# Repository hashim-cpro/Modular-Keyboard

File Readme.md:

<div align="center">
  <a href="https://hackclub.com/highway">
    </img>
  </a>
  
<h1>60% Modular Keyboard</h1>
</div>

It is a 60% wireless keyboard(bluetooth) also works wired. It has magnetic modules. Currently I only added a Numpad but almost anything could be added in a chain as long as it works on i2c.
it has hotswapable switches, rgb lights for each key, OLED, rotoary encoder, dedicated charging module(1000mah) and a 10000mah battery. Also it is kind of MCU agnostic, you can use any XIAO series MCU with it, for example rp2040 if you don't want bluetooth or nRF52840.

# CAD Design

I used shapr3d to make the case, it is not done, I am still working on it, once I am happy with a case I will add it here, but the current case is as follows:

# Wired connections

The charging module and battery are not connected to the PCB electrically, I will use wires for them.

# PCB design

I used KiCad to make the PCB. Here are the schematics:

Here is the PCB:

# Firmware

For Firmware I made two versions:

1. **QMK Firmware**: Works out of the box but it is wired only (no Bluetooth). This is ready to use.
2. **ZMK Firmware**: Supports Bluetooth wireless functionality. This will work only when ZMK is upgraded to Zephyr 3.6 or with a custom driver for the I2C expander.

Both firmware options are available in this repository under the Firmware directory.

# BOM

here's the csv: [Link](https://docs.google.com/spreadsheets/d/1DyREVeE_MUjtT9r5M6x5S8JvudkvJUOvS-f6R7vg9m8/edit?usp=sharing)
| Name | Quantity | Price (USD) | Shipping Cost (USD) | URL |
| ------------------------- | ------------------ | ----------- | ------------------- | --- |
| [Switches](https://www.aliexpress.com/item/1005008458590123.html) | 90 | $35.73 | $0.00 | [Link](https://www.aliexpress.com/item/1005008458590123.html) |
| [Keycaps](https://www.aliexpress.com/item/1005006068241056.html) | 1 | $23.25 | $0.00 | [Link](https://www.aliexpress.com/item/1005006068241056.html) |
| [Hotswapable sockets](https://www.aliexpress.com/item/1005009187521124.html) | 110 | $15.39 | $0.00 | [Link](https://www.aliexpress.com/item/1005009187521124.html) |
| [Stabilizers](https://www.aliexpress.com/item/1005001686299616.html) | 1x set | $10.77 | $0.00 | [Link](https://www.aliexpress.com/item/1005001686299616.html) |
| Custom PCB | 5 | $20.00 | $25.00 | jlcpcb |
| [Magnetic pogo pins](https://www.aliexpress.com/item/1005008564171277.html) | 2x 3p and 2x 4p | $20.28 | $0.00 | [Link](https://www.aliexpress.com/item/1005008564171277.html) |
| [Microcontroller](https://www.aliexpress.com/item/1005007416714633.html) | 1 | $10.27 | $5.00 | [Link](https://www.aliexpress.com/item/1005007416714633.html) |
| [I2C expander](https://www.aliexpress.com/item/1005008705264264.html?spm=a2g0o.productlist.main.11.68e87c79MkEB3P&algo_pvid=652b9ee5-a6ca-4eb2-a04e-750bf44d7567&algo_exp_id=652b9ee5-a6ca-4eb2-a04e-750bf44d7567-10&pdp_ext_f=%7B%22order%22%3A%22-1%22%2C%22eval%22%3A%221%22%7D&pdp_npi=6%40dis%21USD%215.04%215.04%21%21%2136.00%2136.00%21%402101246417554269745763126e6e24%2112000046323693257%21sea%21PK%212630002641%21ABX%211%210%21n_tag%3A-29910%3Bm03_new_user%3A-29895&curPageLogUid=tP3Bol6SwU30&utparam-url=scene%3Asearch%7Cquery_from%3A%7Cx_object_id%3A1005008705264264%7C_p_origin_prod%3A) | 2 | $5.04 | $3.47 | [Link](https://www.aliexpress.com/item/1005008705264264.html?spm=a2g0o.productlist.main.11.68e87c79MkEB3P&algo_pvid=652b9ee5-a6ca-4eb2-a04e-750bf44d7567&algo_exp_id=652b9ee5-a6ca-4eb2-a04e-750bf44d7567-10&pdp_ext_f=%7B%22order%22%3A%22-1%22%2C%22eval%22%3A%221%22%7D&pdp_npi=6%40dis%21USD%215.04%215.04%21%21%2136.00%2136.00%21%402101246417554269745763126e6e24%2112000046323693257%21sea%21PK%212630002641%21ABX%211%210%21n_tag%3A-29910%3Bm03_new_user%3A-29895&curPageLogUid=tP3Bol6SwU30&utparam-url=scene%3Asearch%7Cquery_from%3A%7Cx_object_id%3A1005008705264264%7C_p_origin_prod%3A) |
| [Battery](https://www.aliexpress.com/item/1005001651303033.html) | 1 | $6.30 | $0.00 | [Link](https://www.aliexpress.com/item/1005001651303033.html) |
| [Battery protection module](https://www.aliexpress.com/item/1005007507131765.html) | 1 | $4.00 | $0.00 | [Link](https://www.aliexpress.com/item/1005007507131765.html) |
| Charging module | Will supply myself | $0.00 | $0.00 | - |
| Boost converter | Will supply myself | $0.00 | $0.00 | - |
| Rotatory Encoder | Already owned | $0.00 | $0.00 | - |
| [OLED module](https://www.aliexpress.com/item/1005006351390199.html) | 1 | $5.00 | $0.00 | [Link](https://www.aliexpress.com/item/1005006351390199.html) |
| [SK6812 mini E leds](https://www.aliexpress.com/item/1005008417206409.html) | 100 | $4.88 | $3.11 | [Link](https://www.aliexpress.com/item/1005008417206409.html) |
| [Diodes](https://digilog.pk/products/in4148-1n-4148-diode) | 100 | $1.00 | $1.00 | [Link](https://digilog.pk/products/in4148-1n-4148-diode) |
| **Total** | | **$161.55** | **$43.40** | |
| **Complete Cost** | | **$204.95** | | |

> The complete cost does not include the 3D printed case.

**Important Note**: You might find some of these components cheaper on AliExpress, but trust me, their shipping costs to Pakistan are absolutely insane. I created this BOM keeping Pakistani shipping costs in mind - sometimes paying a bit more upfront is way better than getting hit with crazy shipping fees later. If you're in a different country, definitely check AliExpress for better deals, but for us Pakistanis, this is probably your best bet cost-wise.

Also Ali Express prices tend to change for different regions, so when verifying the BOM, make sure to set the region to Pakistan to get the correct prices.

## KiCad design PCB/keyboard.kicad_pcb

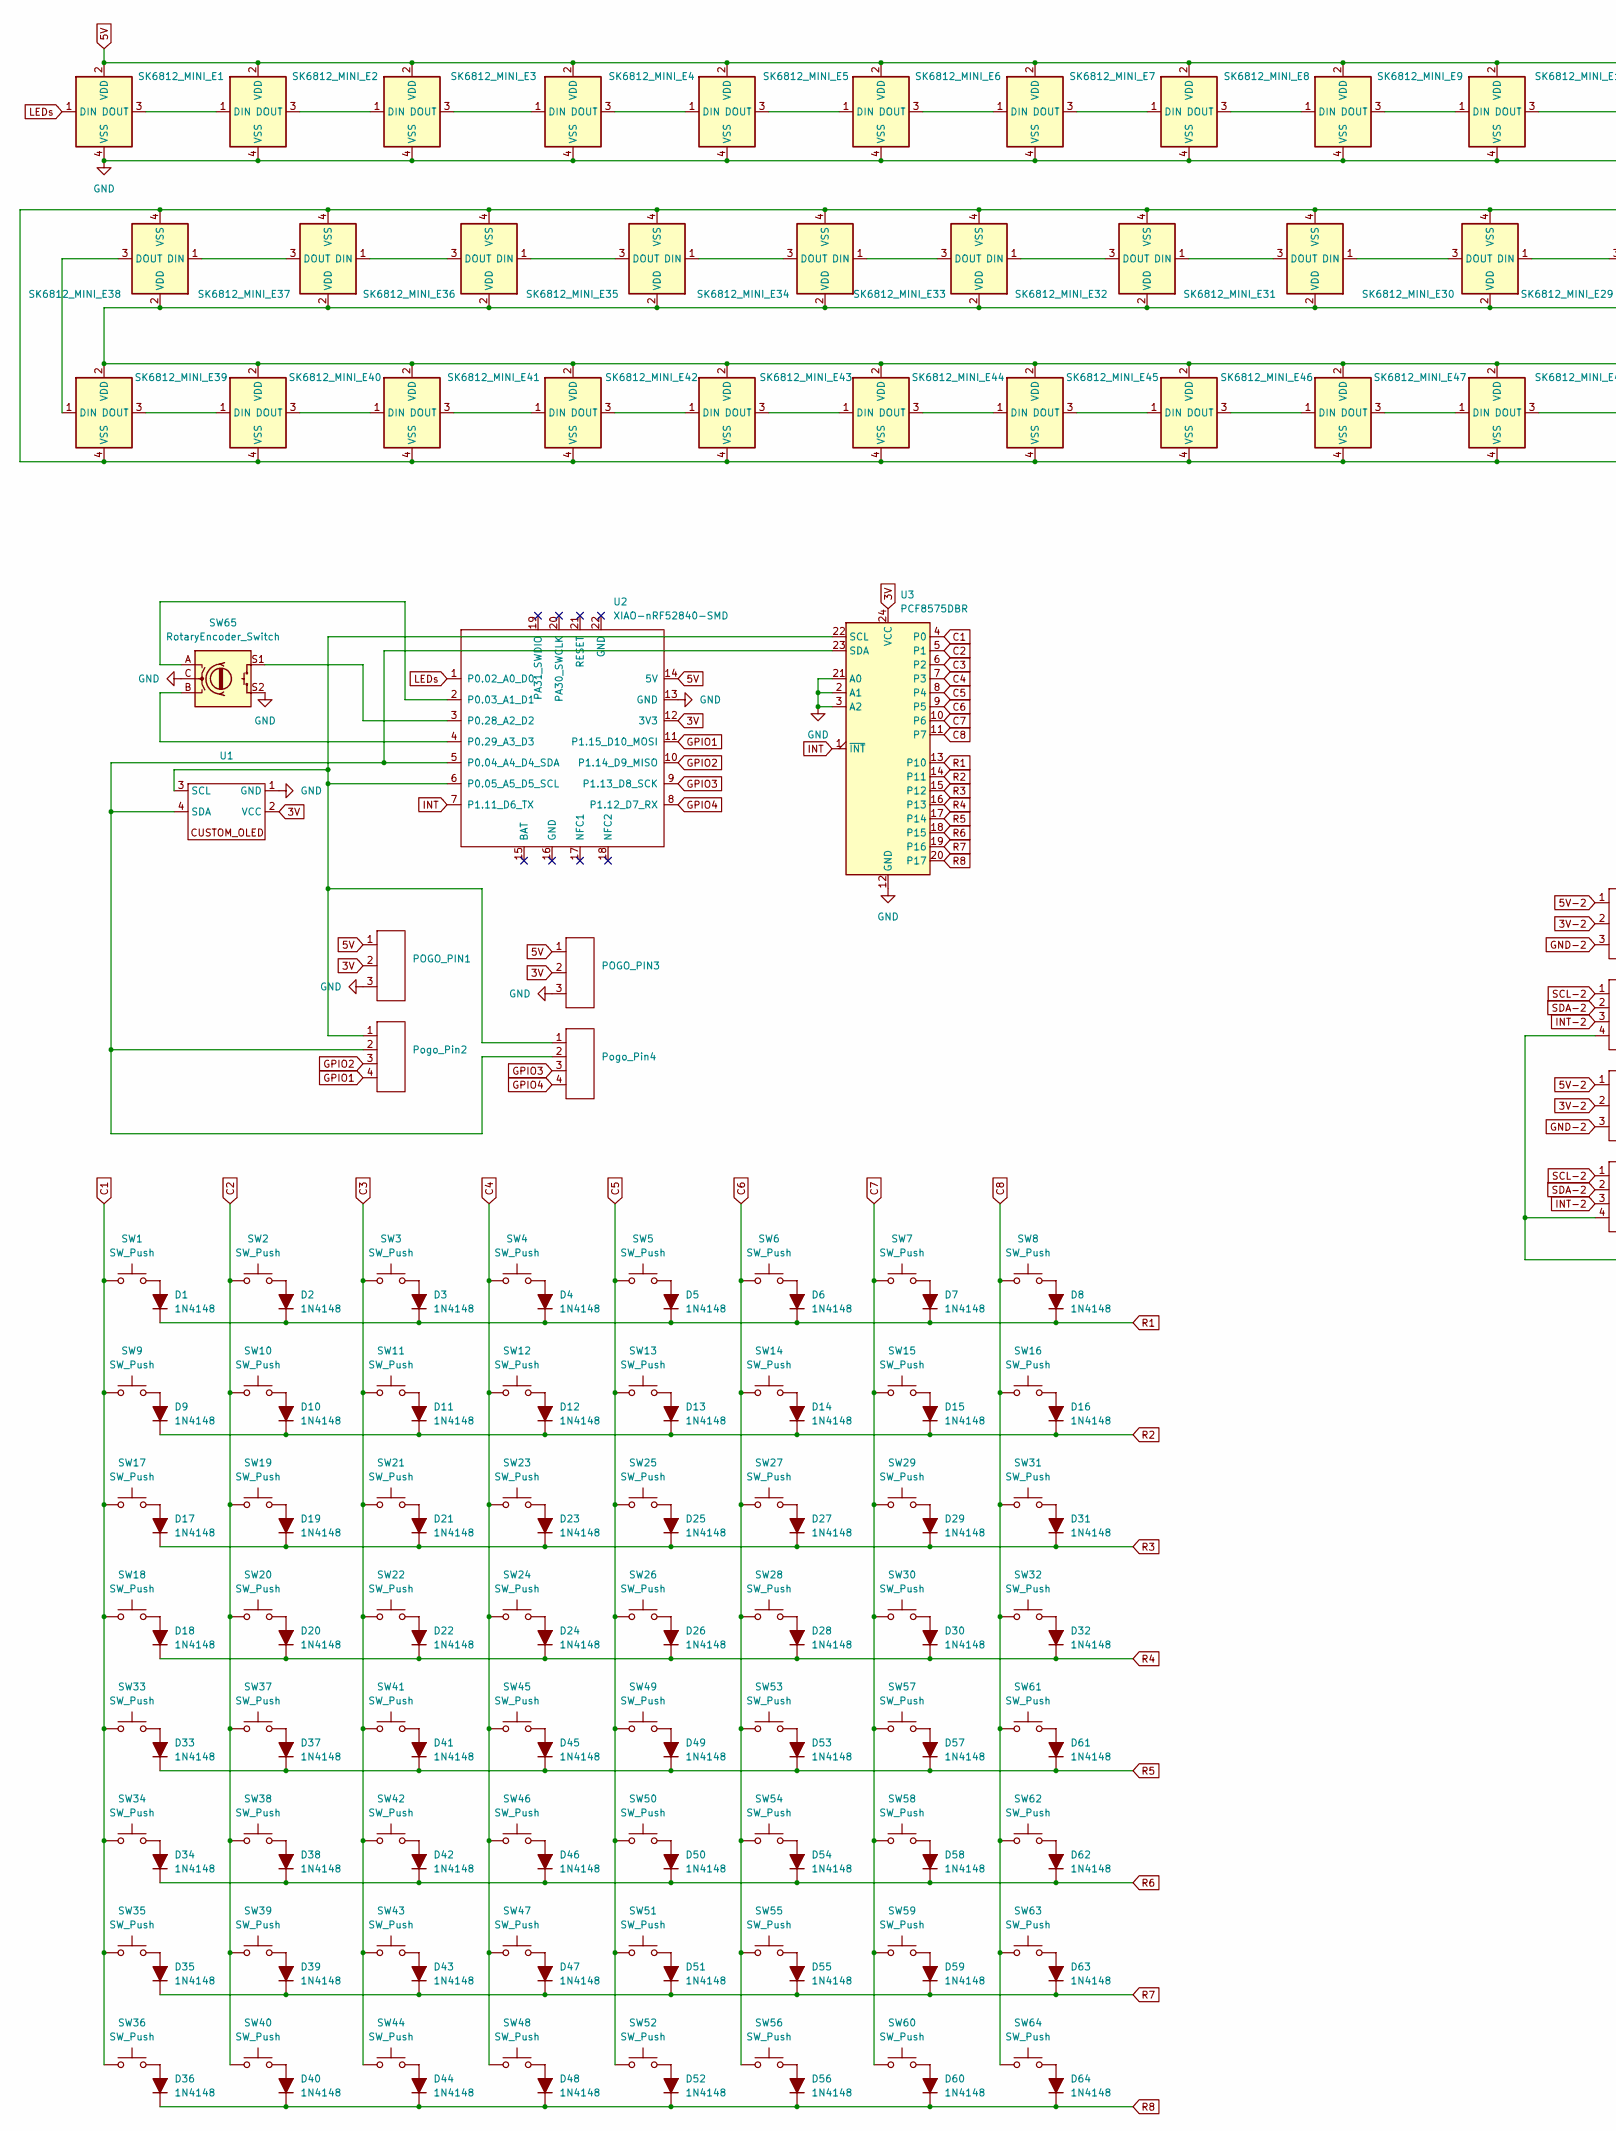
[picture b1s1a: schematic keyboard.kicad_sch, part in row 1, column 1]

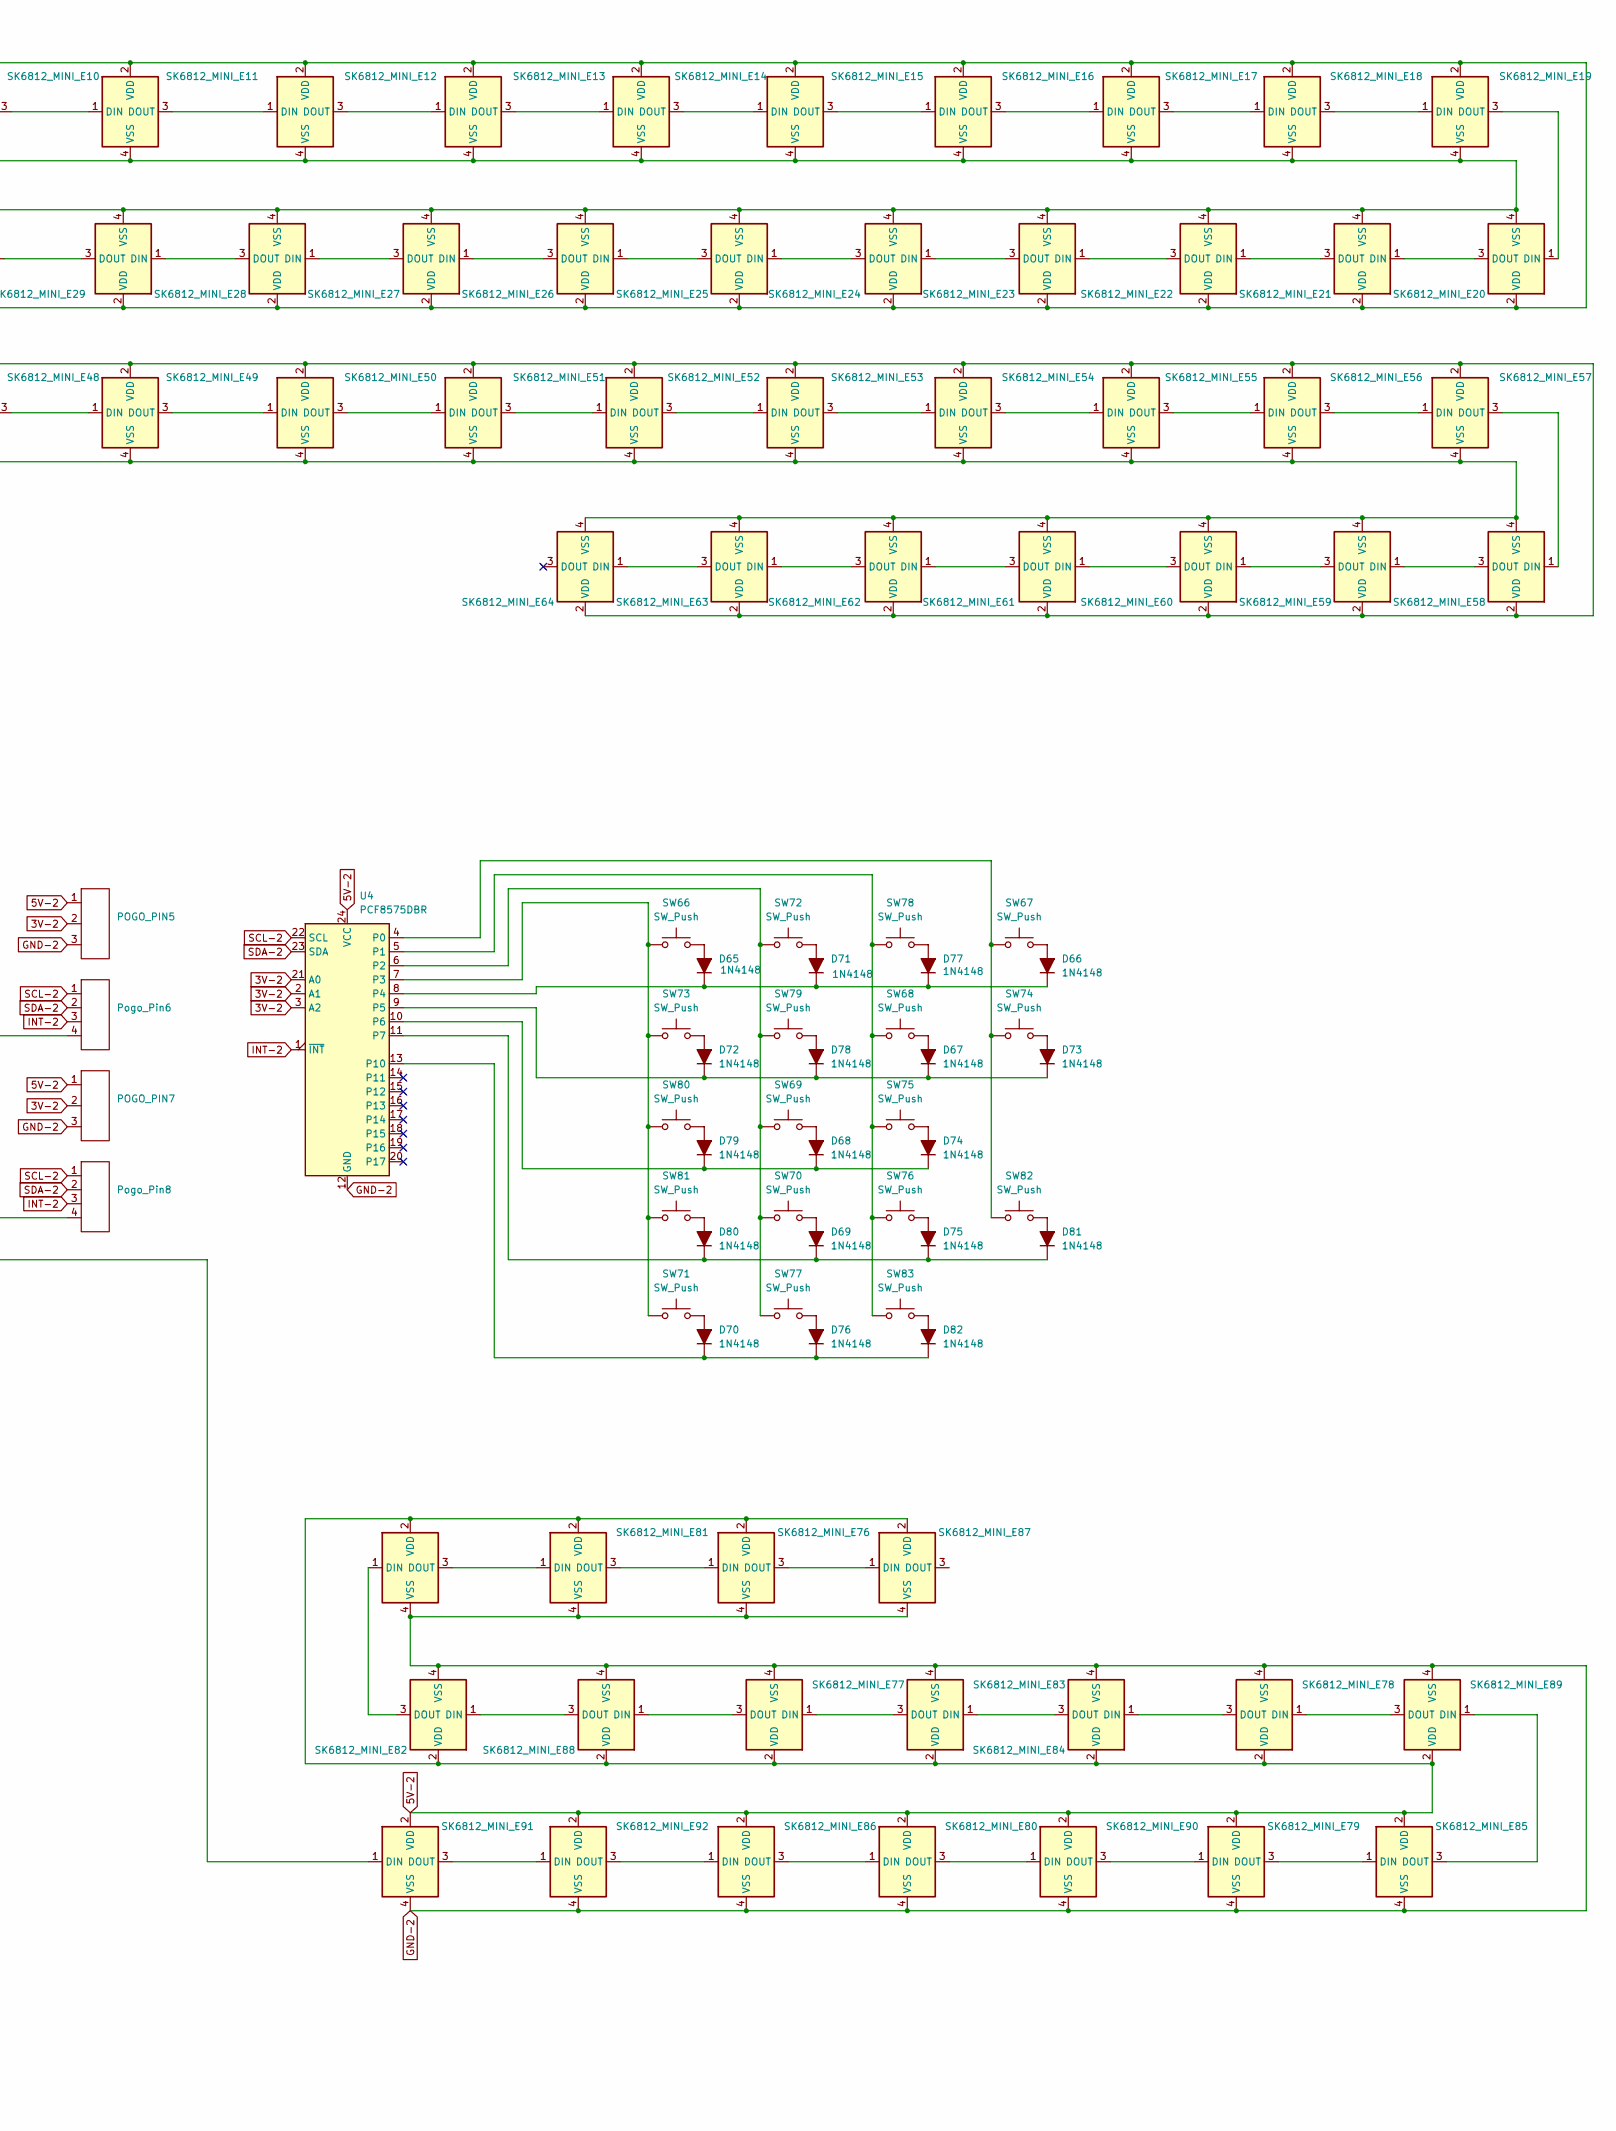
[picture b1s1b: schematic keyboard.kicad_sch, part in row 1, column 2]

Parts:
D1, D2, D3, D4, D5, D6, D7, D8, D9, D10, D11, D12, D13, D14, D15, D16, D17, D18, D19, D20, D21, D22, D23, D24, D25, D26, D27, D28, D29, D30, D31, D32, D33, D34, D35, D36, D37, D38, D39, D40, D41, D42, D43, D44, D45, D46, D47, D48, D49, D50, D51, D52, D53, D54, D55, D56, D57, D58, D59, D60, D61, D62, D63, D64, D65, D66, D67, D68, D69, D70, D71, D72, D73, D74, D75, D76, D77, D78, D79, D80, D81, D82: 1N4148; D_DO-35_SOD27_P7.62mm_Horizontal
POGO_PIN1, POGO_PIN3, POGO_PIN5, POGO_PIN7: Pogo_Pins_3P
Pogo_Pin2, Pogo_Pin4, Pogo_Pin6, Pogo_Pin8: Pogo_Pins_4P
SK6812_MINI_E1, SK6812_MINI_E2, SK6812_MINI_E3, SK6812_MINI_E4, SK6812_MINI_E5, SK6812_MINI_E6, SK6812_MINI_E7, SK6812_MINI_E8, SK6812_MINI_E9, SK6812_MINI_E10, SK6812_MINI_E11, SK6812_MINI_E12, SK6812_MINI_E13, SK6812_MINI_E14, SK6812_MINI_E15, SK6812_MINI_E16, SK6812_MINI_E17, SK6812_MINI_E18, SK6812_MINI_E19, SK6812_MINI_E20, SK6812_MINI_E21, SK6812_MINI_E22, SK6812_MINI_E23, SK6812_MINI_E24, SK6812_MINI_E25, SK6812_MINI_E26, SK6812_MINI_E27, SK6812_MINI_E28, SK6812_MINI_E29, SK6812_MINI_E30, SK6812_MINI_E31, SK6812_MINI_E32, SK6812_MINI_E33, SK6812_MINI_E34, SK6812_MINI_E35, SK6812_MINI_E36, SK6812_MINI_E37, SK6812_MINI_E38, SK6812_MINI_E39, SK6812_MINI_E40, SK6812_MINI_E41, SK6812_MINI_E42, SK6812_MINI_E43, SK6812_MINI_E44, SK6812_MINI_E45, SK6812_MINI_E46, SK6812_MINI_E47, SK6812_MINI_E48, SK6812_MINI_E49, SK6812_MINI_E50, SK6812_MINI_E51, SK6812_MINI_E52, SK6812_MINI_E53, SK6812_MINI_E54, SK6812_MINI_E55, SK6812_MINI_E56, SK6812_MINI_E57, SK6812_MINI_E58, SK6812_MINI_E59, SK6812_MINI_E60, SK6812_MINI_E61, SK6812_MINI_E62, SK6812_MINI_E63, SK6812_MINI_E64, SK6812_MINI_E75, SK6812_MINI_E76, SK6812_MINI_E77, SK6812_MINI_E78, SK6812_MINI_E79, SK6812_MINI_E80, SK6812_MINI_E81, SK6812_MINI_E82, SK6812_MINI_E83, SK6812_MINI_E84, SK6812_MINI_E85, SK6812_MINI_E86, SK6812_MINI_E87, SK6812_MINI_E88, SK6812_MINI_E89, SK6812_MINI_E90, SK6812_MINI_E91, SK6812_MINI_E92: MX_SK6812MINI-E
SW1, SW2, SW3, SW4, SW5, SW6, SW7, SW8, SW9, SW10, SW11, SW12, SW13, SW14, SW15, SW16, SW17, SW18, SW19, SW20, SW21, SW22, SW23, SW24, SW25, SW26, SW27, SW28, SW29, SW30, SW31, SW32, SW33, SW34, SW35, SW36, SW37, SW38, SW39, SW40, SW41, SW42, SW43, SW44, SW45, SW46, SW47, SW48, SW49, SW50, SW51, SW52, SW53, SW54, SW55, SW56, SW57, SW58, SW59, SW60, SW61, SW62, SW63, SW64, SW66, SW67, SW68, SW69, SW70, SW71, SW72, SW73, SW74, SW75, SW76, SW77, SW78, SW79, SW80, SW81, SW82, SW83: SW_Push; SW_Hotswap_Kailh_MX_1.00u
SW65: RotaryEncoder_Switch; RotaryEncoder_Alps_EC11E-Switch_Vertical_H20mm
U1: SSD1306-0.91-OLED-4pin-128x32
U2: XIAO-nRF52840-SMD; XIAO-nRF52840-DIP
U3, U4: PCF8575DBR; SSOP-24_5.3x8.2mm_P0.65mm

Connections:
3V: POGO_PIN1.2, POGO_PIN3.2, U1.2 (VCC), U2.12 (3V3), U3.24 (VCC)
3V-2: POGO_PIN5.2, POGO_PIN7.2, U4.2 (A1), U4.3 (A2), U4.21 (A0)
5V: POGO_PIN1.1, POGO_PIN3.1, SK6812_MINI_E1.2 (VDD), SK6812_MINI_E2.2 (VDD), SK6812_MINI_E3.2 (VDD), SK6812_MINI_E4.2 (VDD), SK6812_MINI_E5.2 (VDD), SK6812_MINI_E6.2 (VDD), SK6812_MINI_E7.2 (VDD), SK6812_MINI_E8.2 (VDD), SK6812_MINI_E9.2 (VDD), SK6812_MINI_E10.2 (VDD), SK6812_MINI_E11.2 (VDD), SK6812_MINI_E12.2 (VDD), SK6812_MINI_E13.2 (VDD), SK6812_MINI_E14.2 (VDD), SK6812_MINI_E15.2 (VDD), SK6812_MINI_E16.2 (VDD), SK6812_MINI_E17.2 (VDD), SK6812_MINI_E18.2 (VDD), SK6812_MINI_E19.2 (VDD), SK6812_MINI_E20.2 (VDD), SK6812_MINI_E21.2 (VDD), SK6812_MINI_E22.2 (VDD), SK6812_MINI_E23.2 (VDD), SK6812_MINI_E24.2 (VDD), SK6812_MINI_E25.2 (VDD), SK6812_MINI_E26.2 (VDD), SK6812_MINI_E27.2 (VDD), SK6812_MINI_E28.2 (VDD), SK6812_MINI_E29.2 (VDD), SK6812_MINI_E30.2 (VDD), SK6812_MINI_E31.2 (VDD), SK6812_MINI_E32.2 (VDD), SK6812_MINI_E33.2 (VDD), SK6812_MINI_E34.2 (VDD), SK6812_MINI_E35.2 (VDD), SK6812_MINI_E36.2 (VDD), SK6812_MINI_E37.2 (VDD), SK6812_MINI_E38.2 (VDD), SK6812_MINI_E39.2 (VDD), SK6812_MINI_E40.2 (VDD), SK6812_MINI_E41.2 (VDD), SK6812_MINI_E42.2 (VDD), SK6812_MINI_E43.2 (VDD), SK6812_MINI_E44.2 (VDD), SK6812_MINI_E45.2 (VDD), SK6812_MINI_E46.2 (VDD), SK6812_MINI_E47.2 (VDD), SK6812_MINI_E48.2 (VDD), SK6812_MINI_E49.2 (VDD), SK6812_MINI_E50.2 (VDD), SK6812_MINI_E51.2 (VDD), SK6812_MINI_E52.2 (VDD), SK6812_MINI_E53.2 (VDD), SK6812_MINI_E54.2 (VDD), SK6812_MINI_E55.2 (VDD), SK6812_MINI_E56.2 (VDD), SK6812_MINI_E57.2 (VDD), SK6812_MINI_E58.2 (VDD), SK6812_MINI_E59.2 (VDD), SK6812_MINI_E60.2 (VDD), SK6812_MINI_E61.2 (VDD), SK6812_MINI_E62.2 (VDD), SK6812_MINI_E63.2 (VDD), SK6812_MINI_E64.2 (VDD), U2.14 (5V)
5V-2: POGO_PIN5.1, POGO_PIN7.1, SK6812_MINI_E75.2 (VDD), SK6812_MINI_E76.2 (VDD), SK6812_MINI_E77.2 (VDD), SK6812_MINI_E78.2 (VDD), SK6812_MINI_E79.2 (VDD), SK6812_MINI_E80.2 (VDD), SK6812_MINI_E81.2 (VDD), SK6812_MINI_E82.2 (VDD), SK6812_MINI_E83.2 (VDD), SK6812_MINI_E84.2 (VDD), SK6812_MINI_E85.2 (VDD), SK6812_MINI_E86.2 (VDD), SK6812_MINI_E87.2 (VDD), SK6812_MINI_E88.2 (VDD), SK6812_MINI_E89.2 (VDD), SK6812_MINI_E90.2 (VDD), SK6812_MINI_E91.2 (VDD), SK6812_MINI_E92.2 (VDD), U4.24 (VCC)
C1: SW1.1, SW9.1, SW17.1, SW18.1, SW33.1, SW34.1, SW35.1, SW36.1, U3.4 (P0)
C2: SW2.1, SW10.1, SW19.1, SW20.1, SW37.1, SW38.1, SW39.1, SW40.1, U3.5 (P1)
C3: SW3.1, SW11.1, SW21.1, SW22.1, SW41.1, SW42.1, SW43.1, SW44.1, U3.6 (P2)
C4: SW4.1, SW12.1, SW23.1, SW24.1, SW45.1, SW46.1, SW47.1, SW48.1, U3.7 (P3)
C5: SW5.1, SW13.1, SW25.1, SW26.1, SW49.1, SW50.1, SW51.1, SW52.1, U3.8 (P4)
C6: SW6.1, SW14.1, SW27.1, SW28.1, SW53.1, SW54.1, SW55.1, SW56.1, U3.9 (P5)
C7: SW7.1, SW15.1, SW29.1, SW30.1, SW57.1, SW58.1, SW59.1, SW60.1, U3.10 (P6)
C8: SW8.1, SW16.1, SW31.1, SW32.1, SW61.1, SW62.1, SW63.1, SW64.1, U3.11 (P7)
GND: POGO_PIN1.3, POGO_PIN3.3, SK6812_MINI_E1.4 (VSS), SK6812_MINI_E2.4 (VSS), SK6812_MINI_E3.4 (VSS), SK6812_MINI_E4.4 (VSS), SK6812_MINI_E5.4 (VSS), SK6812_MINI_E6.4 (VSS), SK6812_MINI_E7.4 (VSS), SK6812_MINI_E8.4 (VSS), SK6812_MINI_E9.4 (VSS), SK6812_MINI_E10.4 (VSS), SK6812_MINI_E11.4 (VSS), SK6812_MINI_E12.4 (VSS), SK6812_MINI_E13.4 (VSS), SK6812_MINI_E14.4 (VSS), SK6812_MINI_E15.4 (VSS), SK6812_MINI_E16.4 (VSS), SK6812_MINI_E17.4 (VSS), SK6812_MINI_E18.4 (VSS), SK6812_MINI_E19.4 (VSS), SK6812_MINI_E20.4 (VSS), SK6812_MINI_E21.4 (VSS), SK6812_MINI_E22.4 (VSS), SK6812_MINI_E23.4 (VSS), SK6812_MINI_E24.4 (VSS), SK6812_MINI_E25.4 (VSS), SK6812_MINI_E26.4 (VSS), SK6812_MINI_E27.4 (VSS), SK6812_MINI_E28.4 (VSS), SK6812_MINI_E29.4 (VSS), SK6812_MINI_E30.4 (VSS), SK6812_MINI_E31.4 (VSS), SK6812_MINI_E32.4 (VSS), SK6812_MINI_E33.4 (VSS), SK6812_MINI_E34.4 (VSS), SK6812_MINI_E35.4 (VSS), SK6812_MINI_E36.4 (VSS), SK6812_MINI_E37.4 (VSS), SK6812_MINI_E38.4 (VSS), SK6812_MINI_E39.4 (VSS), SK6812_MINI_E40.4 (VSS), SK6812_MINI_E41.4 (VSS), SK6812_MINI_E42.4 (VSS), SK6812_MINI_E43.4 (VSS), SK6812_MINI_E44.4 (VSS), SK6812_MINI_E45.4 (VSS), SK6812_MINI_E46.4 (VSS), SK6812_MINI_E47.4 (VSS), SK6812_MINI_E48.4 (VSS), SK6812_MINI_E49.4 (VSS), SK6812_MINI_E50.4 (VSS), SK6812_MINI_E51.4 (VSS), SK6812_MINI_E52.4 (VSS), SK6812_MINI_E53.4 (VSS), SK6812_MINI_E54.4 (VSS), SK6812_MINI_E55.4 (VSS), SK6812_MINI_E56.4 (VSS), SK6812_MINI_E57.4 (VSS), SK6812_MINI_E58.4 (VSS), SK6812_MINI_E59.4 (VSS), SK6812_MINI_E60.4 (VSS), SK6812_MINI_E61.4 (VSS), SK6812_MINI_E62.4 (VSS), SK6812_MINI_E63.4 (VSS), SK6812_MINI_E64.4 (VSS), SW65.C, SW65.S2, U1.1 (GND), U2.13 (GND), U3.2 (A1), U3.3 (A2), U3.12 (GND), U3.21 (A0)
GND-2: POGO_PIN5.3, POGO_PIN7.3, SK6812_MINI_E75.4 (VSS), SK6812_MINI_E76.4 (VSS), SK6812_MINI_E77.4 (VSS), SK6812_MINI_E78.4 (VSS), SK6812_MINI_E79.4 (VSS), SK6812_MINI_E80.4 (VSS), SK6812_MINI_E81.4 (VSS), SK6812_MINI_E82.4 (VSS), SK6812_MINI_E83.4 (VSS), SK6812_MINI_E84.4 (VSS), SK6812_MINI_E85.4 (VSS), SK6812_MINI_E86.4 (VSS), SK6812_MINI_E87.4 (VSS), SK6812_MINI_E88.4 (VSS), SK6812_MINI_E89.4 (VSS), SK6812_MINI_E90.4 (VSS), SK6812_MINI_E91.4 (VSS), SK6812_MINI_E92.4 (VSS), U4.12 (GND)
GPIO1: Pogo_Pin2.4, U2.11 (P1.15_D10_MOSI)
GPIO2: Pogo_Pin2.3, U2.10 (P1.14_D9_MISO)
GPIO3: Pogo_Pin4.3, U2.9 (P1.13_D8_SCK)
GPIO4: Pogo_Pin4.4, U2.8 (P1.12_D7_RX)
INT: U2.7 (P1.11_D6_TX), U3.1 (~INT)
INT-2: Pogo_Pin6.3, Pogo_Pin8.3, U4.1 (~INT)
LEDs: SK6812_MINI_E1.1 (DIN), U2.1 (P0.02_A0_D0)
unnamed: D1.2 (A), SW1.2
unnamed: D2.2 (A), SW2.2
unnamed: D3.2 (A), SW3.2
unnamed: D4.2 (A), SW4.2
unnamed: D5.2 (A), SW5.2
unnamed: D6.2 (A), SW6.2
unnamed: D7.2 (A), SW7.2
unnamed: D8.2 (A), SW8.2
unnamed: D9.2 (A), SW9.2
unnamed: D10.2 (A), SW10.2
unnamed: D11.2 (A), SW11.2
unnamed: D12.2 (A), SW12.2
unnamed: D13.2 (A), SW13.2
unnamed: D14.2 (A), SW14.2
unnamed: D15.2 (A), SW15.2
unnamed: D16.2 (A), SW16.2
unnamed: D17.2 (A), SW17.2
unnamed: D18.2 (A), SW18.2
unnamed: D19.2 (A), SW19.2
unnamed: D20.2 (A), SW20.2
unnamed: D21.2 (A), SW21.2
unnamed: D22.2 (A), SW22.2
unnamed: D23.2 (A), SW23.2
unnamed: D24.2 (A), SW24.2
unnamed: D25.2 (A), SW25.2
unnamed: D26.2 (A), SW26.2
unnamed: D27.2 (A), SW27.2
unnamed: D28.2 (A), SW28.2
unnamed: D29.2 (A), SW29.2
unnamed: D30.2 (A), SW30.2
unnamed: D31.2 (A), SW31.2
unnamed: D32.2 (A), SW32.2
unnamed: D33.2 (A), SW33.2
unnamed: D34.2 (A), SW34.2
unnamed: D35.2 (A), SW35.2
unnamed: D36.2 (A), SW36.2
unnamed: D37.2 (A), SW37.2
unnamed: D38.2 (A), SW38.2
unnamed: D39.2 (A), SW39.2
unnamed: D40.2 (A), SW40.2
unnamed: D41.2 (A), SW41.2
unnamed: D42.2 (A), SW42.2
unnamed: D43.2 (A), SW43.2
unnamed: D44.2 (A), SW44.2
unnamed: D45.2 (A), SW45.2
unnamed: D46.2 (A), SW46.2
unnamed: D47.2 (A), SW47.2
unnamed: D48.2 (A), SW48.2
unnamed: D49.2 (A), SW49.2
unnamed: D50.2 (A), SW50.2
unnamed: D51.2 (A), SW51.2
unnamed: D52.2 (A), SW52.2
unnamed: D53.2 (A), SW53.2
unnamed: D54.2 (A), SW54.2
unnamed: D55.2 (A), SW55.2
unnamed: D56.2 (A), SW56.2
unnamed: D57.2 (A), SW57.2
unnamed: D58.2 (A), SW58.2
unnamed: D59.2 (A), SW59.2
unnamed: D60.2 (A), SW60.2
unnamed: D61.2 (A), SW61.2
unnamed: D62.2 (A), SW62.2
unnamed: D63.2 (A), SW63.2
unnamed: D64.2 (A), SW64.2
unnamed: D65.2 (A), SW66.2
unnamed: D65.1 (K), D66.1 (K), D71.1 (K), D77.1 (K), U4.8 (P4)
unnamed: D66.2 (A), SW67.2
unnamed: D67.2 (A), SW68.2
unnamed: D67.1 (K), D72.1 (K), D73.1 (K), D78.1 (K), U4.9 (P5)
unnamed: D68.2 (A), SW69.2
unnamed: D68.1 (K), D74.1 (K), D79.1 (K), U4.10 (P6)
unnamed: D69.2 (A), SW70.2
unnamed: D69.1 (K), D75.1 (K), D80.1 (K), D81.1 (K), U4.11 (P7)
unnamed: D70.2 (A), SW71.2
unnamed: D70.1 (K), D76.1 (K), D82.1 (K), U4.13 (P10)
unnamed: D71.2 (A), SW72.2
unnamed: D72.2 (A), SW73.2
unnamed: D73.2 (A), SW74.2
unnamed: D74.2 (A), SW75.2
unnamed: D75.2 (A), SW76.2
unnamed: D76.2 (A), SW77.2
unnamed: D77.2 (A), SW78.2
unnamed: D78.2 (A), SW79.2
unnamed: D79.2 (A), SW80.2
unnamed: D80.2 (A), SW81.2
unnamed: D81.2 (A), SW82.2
unnamed: D82.2 (A), SW83.2
unnamed: SK6812_MINI_E1.3 (DOUT), SK6812_MINI_E2.1 (DIN)
unnamed: SK6812_MINI_E2.3 (DOUT), SK6812_MINI_E3.1 (DIN)
unnamed: SK6812_MINI_E3.3 (DOUT), SK6812_MINI_E4.1 (DIN)
unnamed: SK6812_MINI_E4.3 (DOUT), SK6812_MINI_E5.1 (DIN)
unnamed: SK6812_MINI_E5.3 (DOUT), SK6812_MINI_E6.1 (DIN)
unnamed: SK6812_MINI_E6.3 (DOUT), SK6812_MINI_E7.1 (DIN)
unnamed: SK6812_MINI_E7.3 (DOUT), SK6812_MINI_E8.1 (DIN)
unnamed: SK6812_MINI_E8.3 (DOUT), SK6812_MINI_E9.1 (DIN)
unnamed: SK6812_MINI_E9.3 (DOUT), SK6812_MINI_E10.1 (DIN)
unnamed: SK6812_MINI_E10.3 (DOUT), SK6812_MINI_E11.1 (DIN)
unnamed: SK6812_MINI_E11.3 (DOUT), SK6812_MINI_E12.1 (DIN)
unnamed: SK6812_MINI_E12.3 (DOUT), SK6812_MINI_E13.1 (DIN)
unnamed: SK6812_MINI_E13.3 (DOUT), SK6812_MINI_E14.1 (DIN)
unnamed: SK6812_MINI_E14.3 (DOUT), SK6812_MINI_E15.1 (DIN)
unnamed: SK6812_MINI_E15.3 (DOUT), SK6812_MINI_E16.1 (DIN)
unnamed: SK6812_MINI_E16.3 (DOUT), SK6812_MINI_E17.1 (DIN)
unnamed: SK6812_MINI_E17.3 (DOUT), SK6812_MINI_E18.1 (DIN)
unnamed: SK6812_MINI_E18.3 (DOUT), SK6812_MINI_E19.1 (DIN)
unnamed: SK6812_MINI_E19.3 (DOUT), SK6812_MINI_E20.1 (DIN)
unnamed: SK6812_MINI_E20.3 (DOUT), SK6812_MINI_E21.1 (DIN)
unnamed: SK6812_MINI_E21.3 (DOUT), SK6812_MINI_E22.1 (DIN)
unnamed: SK6812_MINI_E22.3 (DOUT), SK6812_MINI_E23.1 (DIN)
unnamed: SK6812_MINI_E23.3 (DOUT), SK6812_MINI_E24.1 (DIN)
unnamed: SK6812_MINI_E24.3 (DOUT), SK6812_MINI_E25.1 (DIN)
unnamed: SK6812_MINI_E25.3 (DOUT), SK6812_MINI_E26.1 (DIN)
unnamed: SK6812_MINI_E26.3 (DOUT), SK6812_MINI_E27.1 (DIN)
unnamed: SK6812_MINI_E27.3 (DOUT), SK6812_MINI_E28.1 (DIN)
unnamed: SK6812_MINI_E28.3 (DOUT), SK6812_MINI_E29.1 (DIN)
unnamed: SK6812_MINI_E29.3 (DOUT), SK6812_MINI_E30.1 (DIN)
unnamed: SK6812_MINI_E30.3 (DOUT), SK6812_MINI_E31.1 (DIN)
unnamed: SK6812_MINI_E31.3 (DOUT), SK6812_MINI_E32.1 (DIN)
unnamed: SK6812_MINI_E32.3 (DOUT), SK6812_MINI_E33.1 (DIN)
unnamed: SK6812_MINI_E33.3 (DOUT), SK6812_MINI_E34.1 (DIN)
unnamed: SK6812_MINI_E34.3 (DOUT), SK6812_MINI_E35.1 (DIN)
unnamed: SK6812_MINI_E35.3 (DOUT), SK6812_MINI_E36.1 (DIN)
unnamed: SK6812_MINI_E36.3 (DOUT), SK6812_MINI_E37.1 (DIN)
unnamed: SK6812_MINI_E37.3 (DOUT), SK6812_MINI_E38.1 (DIN)
unnamed: SK6812_MINI_E38.3 (DOUT), SK6812_MINI_E39.1 (DIN)
unnamed: SK6812_MINI_E39.3 (DOUT), SK6812_MINI_E40.1 (DIN)
unnamed: SK6812_MINI_E40.3 (DOUT), SK6812_MINI_E41.1 (DIN)
unnamed: SK6812_MINI_E41.3 (DOUT), SK6812_MINI_E42.1 (DIN)
unnamed: SK6812_MINI_E42.3 (DOUT), SK6812_MINI_E43.1 (DIN)
unnamed: SK6812_MINI_E43.3 (DOUT), SK6812_MINI_E44.1 (DIN)
unnamed: SK6812_MINI_E44.3 (DOUT), SK6812_MINI_E45.1 (DIN)
unnamed: SK6812_MINI_E45.3 (DOUT), SK6812_MINI_E46.1 (DIN)
unnamed: SK6812_MINI_E46.3 (DOUT), SK6812_MINI_E47.1 (DIN)
unnamed: SK6812_MINI_E47.3 (DOUT), SK6812_MINI_E48.1 (DIN)
unnamed: SK6812_MINI_E48.3 (DOUT), SK6812_MINI_E49.1 (DIN)
unnamed: SK6812_MINI_E49.3 (DOUT), SK6812_MINI_E50.1 (DIN)
unnamed: SK6812_MINI_E50.3 (DOUT), SK6812_MINI_E51.1 (DIN)
unnamed: SK6812_MINI_E51.3 (DOUT), SK6812_MINI_E52.1 (DIN)
unnamed: SK6812_MINI_E52.3 (DOUT), SK6812_MINI_E53.1 (DIN)
unnamed: SK6812_MINI_E53.3 (DOUT), SK6812_MINI_E54.1 (DIN)
unnamed: SK6812_MINI_E54.3 (DOUT), SK6812_MINI_E55.1 (DIN)
unnamed: SK6812_MINI_E55.3 (DOUT), SK6812_MINI_E56.1 (DIN)
unnamed: SK6812_MINI_E56.3 (DOUT), SK6812_MINI_E57.1 (DIN)
unnamed: SK6812_MINI_E57.3 (DOUT), SK6812_MINI_E58.1 (DIN)
unnamed: SK6812_MINI_E58.3 (DOUT), SK6812_MINI_E59.1 (DIN)
unnamed: SK6812_MINI_E59.3 (DOUT), SK6812_MINI_E60.1 (DIN)
unnamed: SK6812_MINI_E60.3 (DOUT), SK6812_MINI_E61.1 (DIN)
unnamed: SK6812_MINI_E61.3 (DOUT), SK6812_MINI_E62.1 (DIN)
unnamed: SK6812_MINI_E62.3 (DOUT), SK6812_MINI_E63.1 (DIN)
unnamed: SK6812_MINI_E63.3 (DOUT), SK6812_MINI_E64.1 (DIN)
unnamed: SK6812_MINI_E75.1 (DIN), SK6812_MINI_E82.3 (DOUT)
unnamed: SK6812_MINI_E75.3 (DOUT), SK6812_MINI_E81.1 (DIN)
unnamed: SK6812_MINI_E76.1 (DIN), SK6812_MINI_E81.3 (DOUT)
unnamed: SK6812_MINI_E76.3 (DOUT), SK6812_MINI_E87.1 (DIN)
unnamed: SK6812_MINI_E77.1 (DIN), SK6812_MINI_E83.3 (DOUT)
unnamed: SK6812_MINI_E77.3 (DOUT), SK6812_MINI_E88.1 (DIN)
unnamed: SK6812_MINI_E78.1 (DIN), SK6812_MINI_E89.3 (DOUT)
unnamed: SK6812_MINI_E78.3 (DOUT), SK6812_MINI_E84.1 (DIN)
unnamed: SK6812_MINI_E79.1 (DIN), SK6812_MINI_E90.3 (DOUT)
unnamed: SK6812_MINI_E79.3 (DOUT), SK6812_MINI_E85.1 (DIN)
unnamed: SK6812_MINI_E80.1 (DIN), SK6812_MINI_E86.3 (DOUT)
unnamed: SK6812_MINI_E80.3 (DOUT), SK6812_MINI_E90.1 (DIN)
unnamed: SK6812_MINI_E82.1 (DIN), SK6812_MINI_E88.3 (DOUT)
unnamed: SK6812_MINI_E83.1 (DIN), SK6812_MINI_E84.3 (DOUT)
unnamed: SK6812_MINI_E85.3 (DOUT), SK6812_MINI_E89.1 (DIN)
unnamed: SK6812_MINI_E86.1 (DIN), SK6812_MINI_E92.3 (DOUT)
unnamed: Pogo_Pin6.4, Pogo_Pin8.4, SK6812_MINI_E91.1 (DIN)
unnamed: SK6812_MINI_E91.3 (DOUT), SK6812_MINI_E92.1 (DIN)
unnamed: Pogo_Pin2.1, Pogo_Pin4.1, U1.3 (SCL), U2.6 (P0.05_A5_D5_SCL), U3.22 (SCL)
unnamed: Pogo_Pin2.2, Pogo_Pin4.2, U1.4 (SDA), U2.5 (P0.04_A4_D4_SDA), U3.23 (SDA)
unnamed: SW65.A, U2.2 (P0.03_A1_D1)
unnamed: SW65.S1, U2.3 (P0.28_A2_D2)
unnamed: SW65.B, U2.4 (P0.29_A3_D3)
unnamed: SW67.1, SW74.1, SW82.1, U4.4 (P0)
unnamed: SW68.1, SW75.1, SW76.1, SW78.1, SW83.1, U4.5 (P1)
unnamed: SW69.1, SW70.1, SW72.1, SW77.1, SW79.1, U4.6 (P2)
unnamed: SW66.1, SW71.1, SW73.1, SW80.1, SW81.1, U4.7 (P3)
R1: D1.1 (K), D2.1 (K), D3.1 (K), D4.1 (K), D5.1 (K), D6.1 (K), D7.1 (K), D8.1 (K), U3.13 (P10)
R2: D9.1 (K), D10.1 (K), D11.1 (K), D12.1 (K), D13.1 (K), D14.1 (K), D15.1 (K), D16.1 (K), U3.14 (P11)
R3: D17.1 (K), D19.1 (K), D21.1 (K), D23.1 (K), D25.1 (K), D27.1 (K), D29.1 (K), D31.1 (K), U3.15 (P12)
R4: D18.1 (K), D20.1 (K), D22.1 (K), D24.1 (K), D26.1 (K), D28.1 (K), D30.1 (K), D32.1 (K), U3.16 (P13)
R5: D33.1 (K), D37.1 (K), D41.1 (K), D45.1 (K), D49.1 (K), D53.1 (K), D57.1 (K), D61.1 (K), U3.17 (P14)
R6: D34.1 (K), D38.1 (K), D42.1 (K), D46.1 (K), D50.1 (K), D54.1 (K), D58.1 (K), D62.1 (K), U3.18 (P15)
R7: D35.1 (K), D39.1 (K), D43.1 (K), D47.1 (K), D51.1 (K), D55.1 (K), D59.1 (K), D63.1 (K), U3.19 (P16)
R8: D36.1 (K), D40.1 (K), D44.1 (K), D48.1 (K), D52.1 (K), D56.1 (K), D60.1 (K), D64.1 (K), U3.20 (P17)
SCL-2: Pogo_Pin6.1, Pogo_Pin8.1, U4.22 (SCL)
SDA-2: Pogo_Pin6.2, Pogo_Pin8.2, U4.23 (SDA)

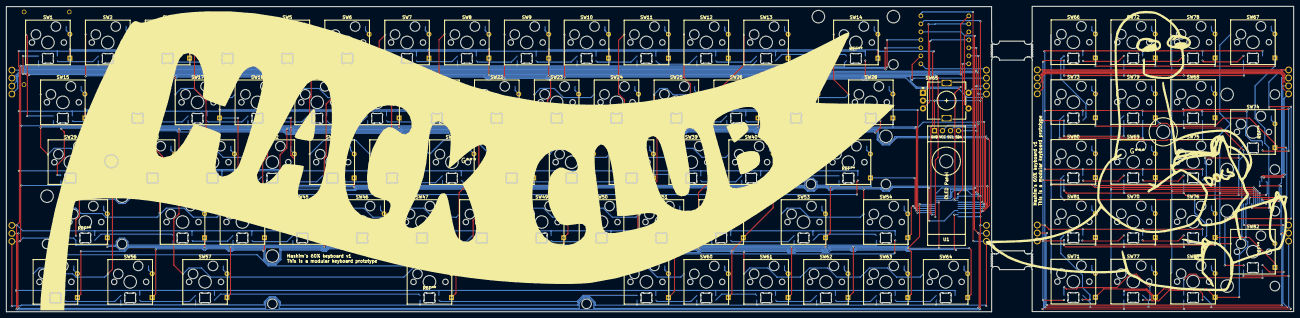
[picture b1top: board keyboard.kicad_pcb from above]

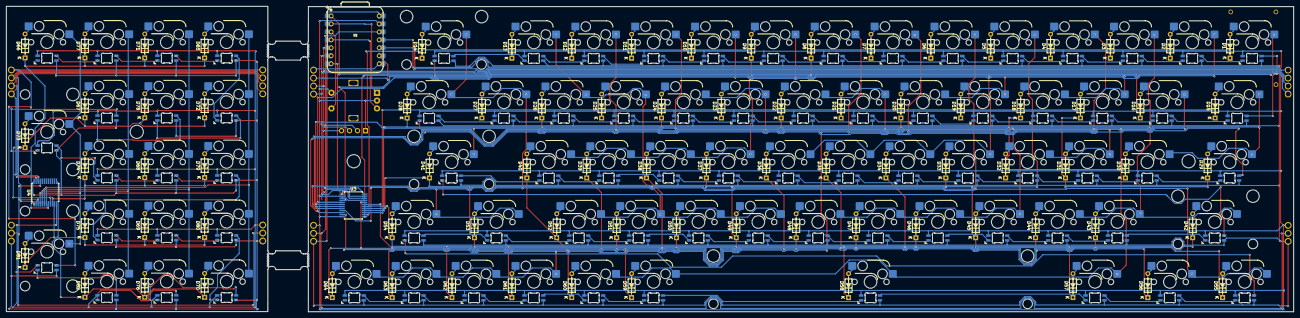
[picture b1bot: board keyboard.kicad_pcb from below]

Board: 2 copper layers, 409.7 x 97.2 mm, 260 parts (85 on the bottom side), 208 nets.

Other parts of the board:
TP4056_Type_C_Charger: Charger; Pogo_Pins_4P

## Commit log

2025-08-01 dd journal
2025-08-01 update journal
2025-08-01 add readme
2025-08-02 add BOM
2025-08-02 add csv link
2025-08-02 update wiring
2025-08-02 fix typo
2025-08-03 add QMk firmware + updae BOM
2025-08-03 fix type
2025-08-04 update BOM to include OLED
2025-08-05 update BOM to include diodes and leds
2025-08-05 add note
2025-08-06 update BOM to include cheaper switches + update time spent on firmware
2025-08-17 include cheaper IO expanders
2025-08-30 Update README with project details and badge
    Added project description and Hack Club badge to README.
